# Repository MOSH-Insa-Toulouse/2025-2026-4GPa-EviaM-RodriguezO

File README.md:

# 2025-2026-4GPa-EviaM-RodriguezO

# Projet Capteur
Dans le cadre du UF « Du capteur au banc de test », ce travail doit concevoir et mettre en œuvre un système de mesure de déformation par un capteur en graphite, lowtech, et comparer son débrouillement à un autre capteur commercial.
Le principe de fonctionnement du capteur en graphite est expliqué comme: La mine de crayon est déposée mécaniquement à la surface du papier, où elle s’insère partiellement dans sa structure poreuse. Cette opération conduit à la formation d’une piste conductrice constituée de particules de graphite dispersées au sein des fibres cellulosiques du papier, le liant jouant principalement un rôle isolant. L’ensemble des particules établit un réseau conducteur dont la continuité dépend du nombre de contacts électriques entre les grains de graphite. Le état du capteur dédnad, la géométrie dépend de la manière dont on s'en sert: une traction tend à éloigner les particules et à réduire les points de contact, tandis qu’une compression favorise leur rapprochement et augmente les connexions conductrices. Ces variations de connectivité se traduisent par une modification mesurable de la résistance électrique de la piste.
La figure suivante illustre, dans la partie c), le fonctionnement du réservoir de graphite sur le feuille:

<p align="center">
Répresentation du graphite
</p>
## Objectifs du projet
- Concevoir et réaliser un shield Arduino intégrant un capteur de contrainte en graphite de conception simple afin d'en déterminer les caractéristiques.
- Concevoir un circuit électronique analogique capable de transmettre des données via un microcontrôleur à une application Android, ainsi que la mise en place d'un banc d'essai.
- Élaboration de la datasheet du capteur.

## Contexte
Nous avons fabriqué un capteur de déformation en exploitant la conductivité d'une couche de graphite appliquée sur une feuille de papier, créant ainsi un capteur grâce aux propriétés granulaires acquises qui dépendent également de la composition du crayon.

Lorsque le capteur est comprimé, la résistance diminue en raison de la proximité des molécules de graphite, ce qui augmente la conductivité. Lorsqu'il est étiré, c'est l'inverse qui se produit, ce qui augmente la résistance.

C'est sur la base de ce comportement que l'on cherche à déduire l'angle d'inclinaison afin de connaître et de rendre compte des caractéristiques du capteur.

Ce projet est basé du travail trouvé dans: Lin, CW, Zhao, Z., Kim, J. et al. (2014); Nature, "Pencil Drawn Strain Gauges and Chemiresistors on Paper".

## Livrables

### KiCad
Pour créer la carte qui nous permettrait de disposer de notre circuit, il a fallu réaliser la conception à l'aide du logiciel KiCad, en tenant compte de tous les composants et en utilisant les connexions convenues en cours.

<p align="center">
Schéma du circuit sur KiCad.
</p>

Après avoir déterminé les connexions du circuit, nous avons pu passer à la conception du circuit imprimé, qui devait tenir compte de certains aspects tels que l'optimisation de l'espace, la largeur minimale des pistes tant pour la transmission des données que pour l'alimentation, la résolution possible lors de l'impression, ainsi que la disposition des composants afin d'éviter d'avoir à souder trop de ponts.

<p align="center">
Dessin du circuit imprimé sur KiCad.
</p>

Voir la documentation dans le dossier **Fichiers Kicad**

### Shield
Le modèle 3D du système créé, y compris sa couverture, est présenté dans l'image suivante.

<p align="center">
Système pret pour être implementé
</p>

Afin de mieux présenter les composants, nous allons nous appuyer sur la figure suivante, qui nous permet de voir tous les éléments qui composent le projet, à commencer par le microcontrôleur Arduino, qui assure la conversion des signaux analogiques en signaux numériques ainsi que le contrôle et la coordination des différentes fonctions ; le capteur low-tech qui sera mis à l'épreuve ; le capteur commercial, afin de pouvoir le comparer à un produit en principe mieux adapté à l'objectif ; l'encodeur, qui permet de sélectionner les fonctions et de les commander manuellement; l'écran OLED, qui nous permet de disposer d'une interface pour sélectionner et contrôler manuellement les fonctions, ainsi que pour afficher les données transmises par les capteurs ; et enfin, le module Bluetooth, qui permet de recevoir les données des capteurs et de les afficher dans l'application mobile.

<p align="center">
Dispositif sans boîtier de protection
</p>

Ces images peuvent être visualisées dans le dossier **3D designs**

### Code Arduino
Le code Arduino a pour but de permettre à l'utilisateur d'interagir avec tous les composants du système : 

- Le contrôle du servomoteur
  - Modification de l'angle d'inclinaison.
  
- Le réglage du potentiomètre numérique
  - Ajustement du gain du système.

- L'affichage local
  - Visualisation en temps réel des données sur l'écran OLED.

- La communication Bluetooth
  - Transmission des données des deux capteurs vers l'application mobile.
 > [!TIP]
> Vous pouvez utiliser l'encodeur numérique pour naviguer dans le menu de l'écran OLED et sélectionner les paramètres souhaités. Cliquez pour accéder au menu de votre choix et maintenez le bouton de l'encodeur enfoncé pour revenir au menu principal.
### Logiciel pour portables
Grâce à la plateforme MIT App Inventor, nous avons conçu une application dont la fonction principale était de pouvoir recevoir et représenter graphiquement les données captées par un ou les deux capteurs simultanément, ainsi que de pouvoir envoyer des données pour commander à la fois le servomoteur et le potentiomètre numérique ; toutefois, l'envoi de données n'a pas eu lieu.

<p align="center">
Application crée, face-avant au démarrage / avec les fonctions.
</p>

Le code des blocs derrière l'interface est visible sur les images suivantes.

<p align="center">
Bloques de code.
</p>

Voir la documentation dans le dossier **Application Mobile**.
### Datasheet
Toutes les spécifications du capteur, sa caractérisation et sa simulation dans le logiciel LTspice sont disponibles dans la fiche technique: [Datasheet](Datasheets/Datasheet_MOSH_EN.pdf)
# Caractérisation du système 
La réponse du capteur à la manipulation a été caractérisée à l'aide de deux types différents de feuilles de graphite : de type HB et de type 3HB. En faisant varier la résistance du potentiomètre, on a constaté que la tension maximale du capteur était atteinte lorsque le potentiomètre avait un gain de 225. 

<p align="center">
Caractérisation du capteur.
</p>

## Conclusion 
Ce projet nous a permis de voir concrètement comment exploiter un phénomène physique pour mesurer un changement au sein d'un système ; en recourant à des moyens simples et en tirant parti de propriétés microscopiques, nous avons pu concevoir un dispositif qui nous a permis de collecter et de traiter des données de manière relativement simple.

Cependant, le projet a également mis en évidence les limites de l'utilisation de ce type de systèmes low-tech, à commencer par la capacité à reproduire les mêmes résultats, car il existe un grand nombre de variables à prendre en compte, telles que l'état du papier, la composition du graphite, la qualité du trait tracé ; toutes ces variables affectent le fonctionnement et l'étalonnage du capteur, et sont difficiles à normaliser manuellement. Et, parallèlement, certaines de ces variables étant très sensibles à l'utilisation, cela finit par nuire à la fiabilité des données recueillies au fil du temps-
Pour toute question concernant les caractéristiques du capteur ou en cas de problèmes techniques, n'hésitez pas à contacter :
- Octavio Rodriguez : orodriguez-r@insa.toulouse.fr
- Manuel Evia : mevia@insa-toulouse.fr

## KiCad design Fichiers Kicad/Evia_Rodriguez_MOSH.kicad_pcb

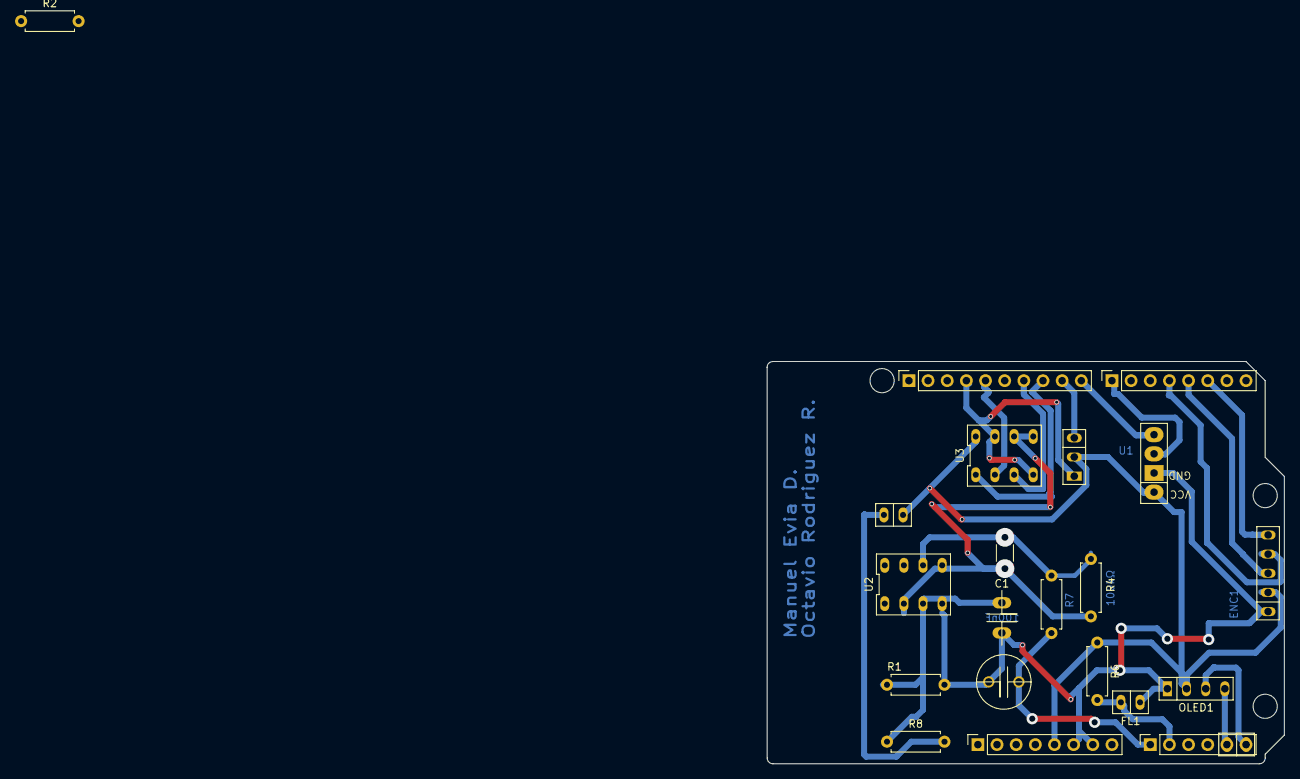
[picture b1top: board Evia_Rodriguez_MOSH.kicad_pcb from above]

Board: 2 copper layers, 68.6 x 53.3 mm, 25 parts (0 on the bottom side), 19 nets.

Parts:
C1, C3: 100nF; CPA_2
C2: 1µF; C_1808_4520Metric
ENC1: SIP-5
FL1, FL1#2: SIP-2
GS1: SIP-2
J1: Power; PinSocket_1x08_P2.54mm_Vertical
J2: Digital/PWM; PinSocket_1x10_P2.54mm_Vertical
J3: Analog; PinSocket_1x06_P2.54mm_Vertical
J4: Digital/PWM; PinSocket_1x08_P2.54mm_Vertical
M1: Motor_Servo; SIP-3
MH1, MH3, MH4: MountingHole_3.2mm
OLED1: SIP-4
R1, R4: 100kΩ; R_Axial_DIN0207_L6.3mm_D2.5mm_P7.62mm_Horizontal
R2, R6, R8: 10kΩ; R_Axial_DIN0207_L6.3mm_D2.5mm_P7.62mm_Horizontal
R7: 1kΩ; R_Axial_DIN0207_L6.3mm_D2.5mm_P7.62mm_Horizontal
U1: Bluetooth_HC05
U2: LTC1050ACN8_PBF; MPC41010
U3: MCP41010; MPC41010

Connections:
+5V: ENC1.2 (+), GS1.1, J1.5, M1.2 (+), OLED1.2 (VCC), R6.1, U1.1 (VCC), U2.7 (V+), U3.8 (VDD)
A1: FL1#2.1, J3.2, R6.2
A4: J3.5, OLED1.4 (SDA)
A5: J3.6, OLED1.3 (SCL)
ADC: C3.1, J3.1, R7.2
D2: ENC1.5 (CLK), J4.6
D3: ENC1.3 (SW), J4.5
D4: ENC1.4 (DT), J4.4
D7: J4.1, U1.3 (TXD)
D8: J2.10, U1.4 (RXD)
D9: J2.9, M1.1 (PWM)
D10: J2.8, U3.1 (~CS)
D11: J2.7, U3.3 (SI)
D13: J2.5, U3.2 (SCK)
GND: C1.2, C3.2, ENC1.1 (GND), FL1#2.2, J1.6, J1.7, J2.4, M1.3 (-), OLED1.1 (GND), R1.2, U1.2 (GND), U2.4 (V-), U3.4 (VSS), U3.7 (PB0)
unnamed: GS1.2, R8.2
unnamed: C1.1, R1.1, R8.1, U2.3 (+IN)
unnamed: C2.2, R4.2, R7.1, U2.6 (OUT)
R2+: C2.1, R4.1, U2.2 (-IN), U3.5 (PA0), U3.6 (PW0)

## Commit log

2026-05-29 Update README.md
    Initial change
2026-05-29 Create temporal
2026-05-29 Create Modèles 3D pour Kicad
2026-05-29 Rename CODE_SinBT.ino to Evia_Rodriguez_MOSH_code.ino
2026-05-29 Rename wwwww.step to CapteurGraphite.step
2026-05-29 Update README.md
    titulos
2026-05-29 Update README.md
    presentacion pequeña
2026-05-29 objectifs
2026-05-29 contexto
    constexo
2026-05-29 lien au dossier
    kika
2026-05-29 kicad shcema
2026-05-29 aplicacion
2026-05-29 imagenes app
2026-05-29 conclusion y alineamiento de imagen de app
2026-05-29 puntos
2026-05-29 Rename image.png to Système.png
2026-05-29 shield
2026-05-29 detalles shield
2026-05-29 Enhance README with Arduino code functionalities
    Added details about the Arduino code functionalities including servo control, digital potentiometer adjustment, local display, and Bluetooth communication.
2026-05-29 la fin
2026-05-31 Add sensor characterization details to README
    Added characterization section for sensor response and included an image.
2026-05-31 Change image source in README for sensor characterization
    Updated image source for sensor characterization.
2026-05-31 Replace images in README with new dimensions
    Updated images in the system characterization section.
2026-05-31 Adjust image sizes in sensor characterization section
    Updated image dimensions for sensor characterization.
2026-05-31 Update README with project details and contact info
    Added project objectives, context, deliverables, and contact information.
2026-05-31 Revise conclusion and add contact details
    Updated the conclusion section and added contact information for technical inquiries.
2026-05-31 Revise README with new graphite representation and image
    Updated the README to include a new image and modified text regarding the graphite sensor.
